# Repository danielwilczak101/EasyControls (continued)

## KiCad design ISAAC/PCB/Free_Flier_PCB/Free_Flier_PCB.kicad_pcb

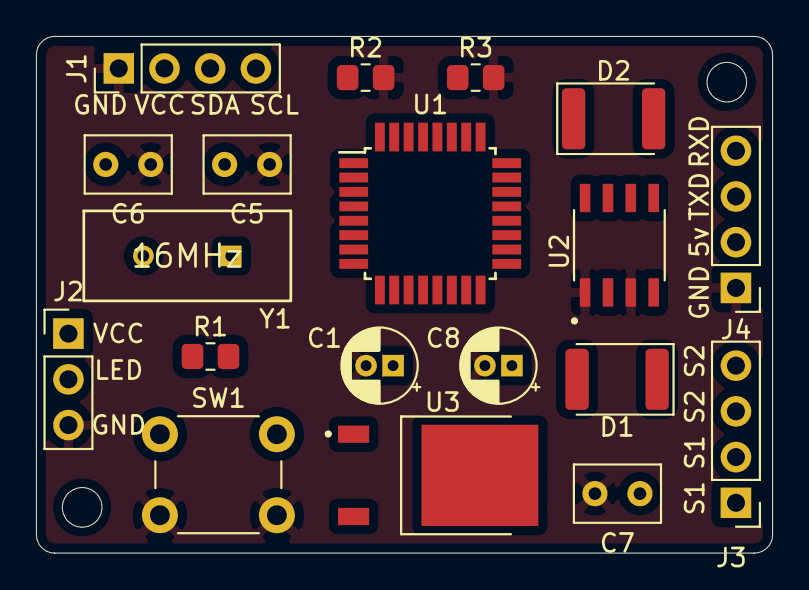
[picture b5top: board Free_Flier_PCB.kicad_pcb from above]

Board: 2 copper layers, 40.9 x 28.7 mm, 21 parts (0 on the bottom side), 12 nets, no tracks yet.

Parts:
C1: 10uF; CP_Radial_D4.0mm_P1.50mm
C5, C6: 22pF; C_Rect_L4.6mm_W3.0mm_P2.50mm_MKS02_FKP02
C7: 0.33uF; C_Rect_L4.6mm_W3.0mm_P2.50mm_MKS02_FKP02
C8: 0.1uF; CP_Radial_D4.0mm_P1.50mm
D1, D2: DIODE; D_1812_4532Metric_Pad1.30x3.40mm_HandSolder
H1, H2: MountingHole; MountingHole_2.2mm_M2
J1: Power and Data Female; PinHeader_1x04_P2.54mm_Vertical
J2: LED Female; PinHeader_1x03_P2.54mm_Vertical
J3: Solenoid Conn; PinHeader_1x04_P2.54mm_Vertical
J4: Programming Pins Female; PinHeader_1x04_P2.54mm_Vertical
R1, R2, R3: 10K; R_0805_2012Metric_Pad1.20x1.40mm_HandSolder
SW1: SW_Push_Dual; SW_PUSH_6mm
U1: ATmega328P-AU; TQFP-32_7x7mm_P0.8mm
U2: DMN4026SSD; SOIC127P600X150-8N
U3: LM78M05CDTX/NOPB; TO228P991X255-3N
Y1: 16MHz; Abracon-ABL-16.000MHZ-B2-0

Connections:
+5V: C1.1, C8.1, J4.2, R1.1, SW1.1, U1.4 (VCC), U1.6 (VCC), U1.18 (AVCC), U1.20 (AREF), U3.1 (OUT)
/Gate1: R2.1, U1.10 (PD6), U2.2 (G1)
/Gate2: R3.1, U1.11 (PD7), U2.4 (G2)
/LED: J2.2, U1.9 (PD5)
/RXD: J4.4, U1.30 (PD0)
/SCL: J1.4, U1.28 (PC5)
/SDA: J1.3, U1.27 (PC4)
/SOL1: D1.1 (K), J3.1, U2.5 (D1), U2.6 (D1)
/SOL2: D2.1 (K), J3.3, U2.7 (D2), U2.8 (D2)
/TXD: J4.3, U1.31 (PD1)
GND: C1.2, C5.1, C6.1, C7.2, C8.2, J1.1, J2.3, J4.1, R2.2, R3.2, SW1.2, U1.3 (GND), U1.5 (GND), U1.21 (GND), U2.1 (S1), U2.3 (S2)
VCC: C7.1, D1.2 (A), D2.2 (A), J1.2, J2.1, J3.2, J3.4, U3.3 (IN)

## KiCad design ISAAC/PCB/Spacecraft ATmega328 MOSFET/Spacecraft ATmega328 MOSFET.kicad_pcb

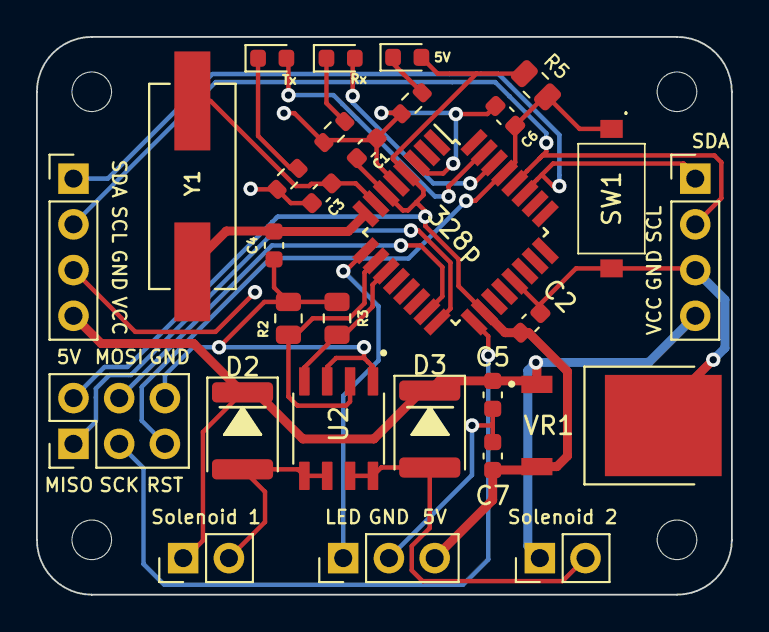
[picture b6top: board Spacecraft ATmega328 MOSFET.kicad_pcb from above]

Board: 2 copper layers, 38.6 x 31.0 mm, 33 parts (0 on the bottom side), 21 nets.

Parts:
5V: LED; LED_0603_1608Metric
328p: ATmega328P-AU; TQFP-32_7x7mm_P0.8mm
C1, C2, C6: 100nF; C_0603_1608Metric
C3, C4: 22pf; C_0603_1608Metric
C5: 0.33 uF; C_0603_1608Metric
C7: 0.1uF; C_0603_1608Metric
D2, D3: D; D_1812_4532Metric
H1, H2, H3, H4: MountingHole; MountingHole_2.2mm_M2
J1, J2: I2C/Power_IN; PinHeader_1x04_P2.54mm_Vertical
J3: Bootloader Pins; PinHeader_2x03_P2.54mm_Vertical
J4: LED; PinHeader_1x03_P2.54mm_Vertical
J5: SOL_1; PinHeader_1x02_P2.54mm_Vertical
Jv: SOL_2; PinHeader_1x02_P2.54mm_Vertical
R2, R3, R5: 10k; R_0805_2012Metric
R6, R7, R8: 300; R_0603_1608Metric
Rx: LED; LED_0603_1608Metric
SW1: SW_Push; PTS636SK25SMTRLFS
Tx: LED; LED_0603_1608Metric
U2: DMN4026SSD; SOIC127P600X150-8N
VR1: LM78M05CDTX_NOPB; TO228P991X255-3N
Y1: Crystal; XTAL_ECS-160-20-5PXDN-TR

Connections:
+5V: 5V.2, 328p.4, 328p.6, 328p.18, C1.1, C2.1, C7.1, J3.2, J4.3, R5.1, VR1.3
/Gate1: 328p.10, R2.1, U2.2
/Gate2: 328p.11, R3.1, U2.4
/LED: 328p.9, J4.1
/MISO: 328p.16, J3.1
/MOSI: 328p.15, J3.4
/RXD: 328p.30, Rx.2
/Reset: 328p.29, C6.2, J3.5, R5.2, SW1.1
/SCK: 328p.17, J3.3
/SCL: 328p.28, J1.2, J2.2
/SDA: 328p.27, J1.1, J2.1
/SOL1: D2.2, J5.2, U2.5, U2.6
/SOL2: D3.2, Jv.2, U2.7, U2.8
/TXD: 328p.31, Tx.2
GND: 328p.3, 328p.5, 328p.21, C1.2, C2.2, C3.1, C4.1, C5.2, C6.1, C7.2, J1.3, J2.3, J3.6, J4.2, R2.2, R3.2, R6.1, R7.1, R8.1, SW1.2, U2.1, U2.3, VR1.4
unnamed: 328p.7, C3.2, Y1.1
unnamed: 328p.8, C4.2, Y1.2
unnamed: 5V.1, R6.2
unnamed: R7.2, Tx.1
unnamed: R8.2, Rx.1
VCC: C5.1, D2.1, D3.1, J1.4, J2.4, J5.1, Jv.1, VR1.1

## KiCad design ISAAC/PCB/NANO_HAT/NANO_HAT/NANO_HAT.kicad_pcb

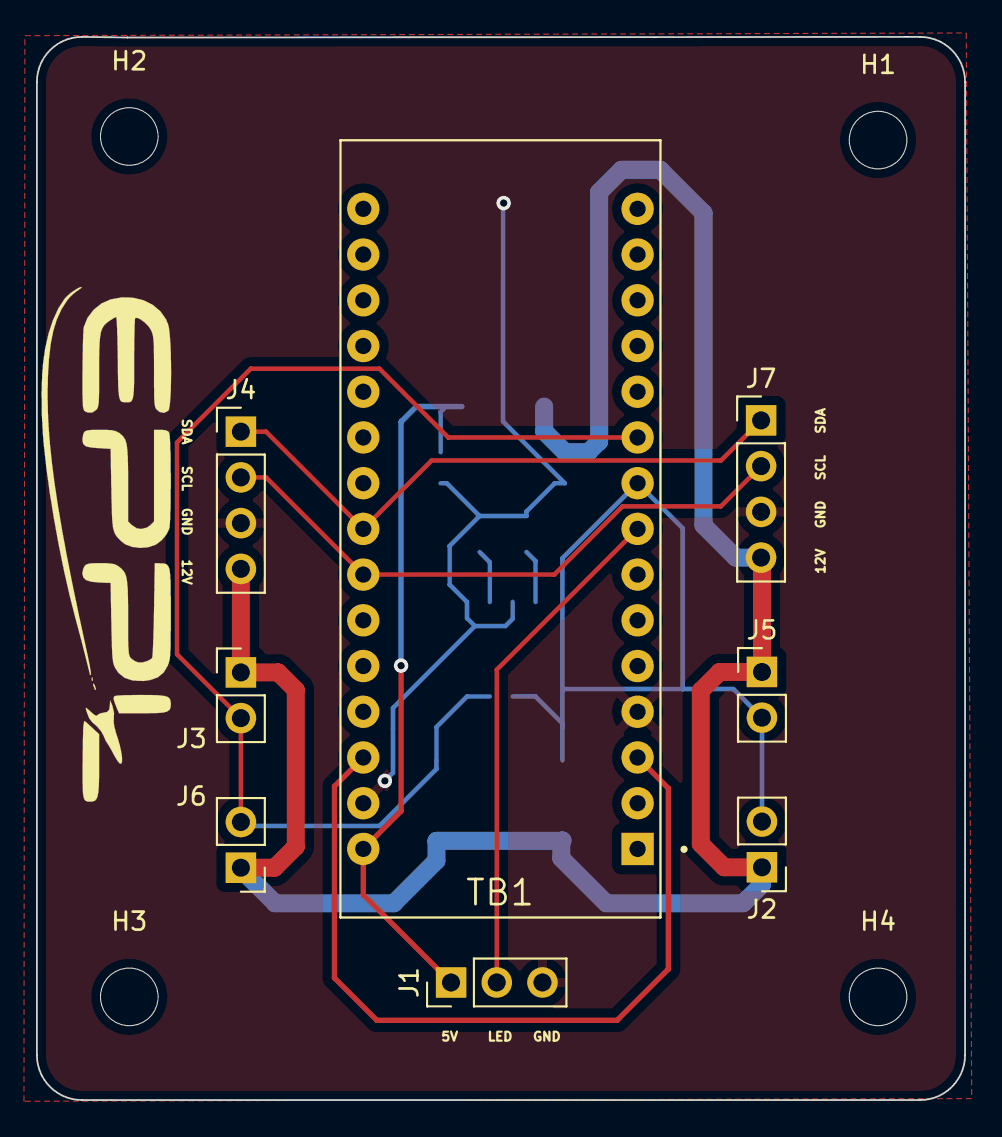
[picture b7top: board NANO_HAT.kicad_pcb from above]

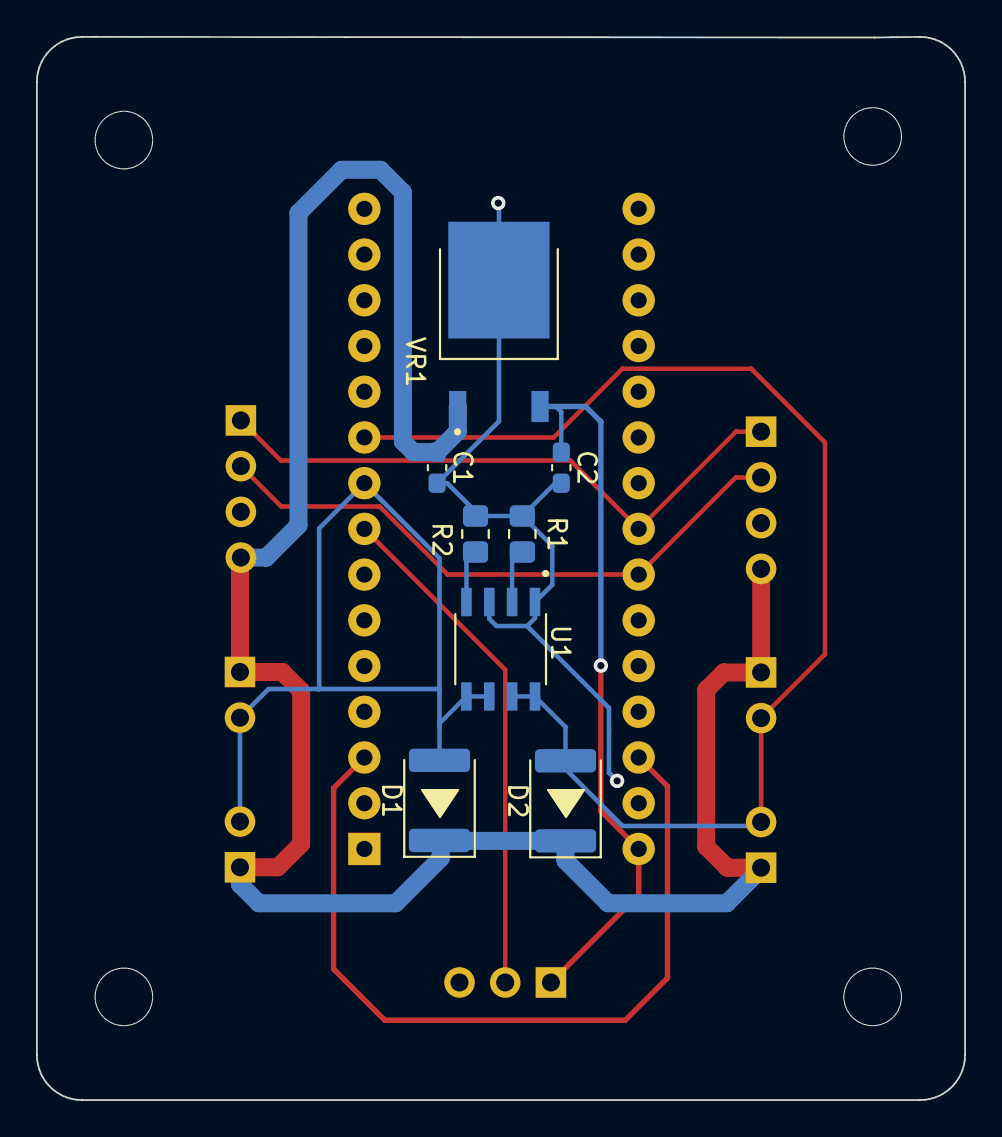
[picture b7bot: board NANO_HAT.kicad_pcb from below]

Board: 2 copper layers, 51.6 x 59.1 mm, 20 parts (8 on the bottom side), 10 nets.

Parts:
C1: 0.33 uF; C_0603_1608Metric_Pad1.08x0.95mm_HandSolder
C2: 0.1uF; C_0603_1608Metric_Pad1.08x0.95mm_HandSolder
D1, D2: D; D_1812_4532Metric_Pad1.30x3.40mm_HandSolder
H1, H2, H3, H4: MountingHole; MountingHole_3.2mm_M3
J1: Conn_01x03_Male; PinHeader_1x03_P2.54mm_Vertical
J2, J3, J5, J6: Conn_01x02_Male; PinHeader_1x02_P2.54mm_Vertical
J4, J7: Conn_01x04_Male; PinHeader_1x04_P2.54mm_Vertical
R1, R2: 10k; R_0805_2012Metric_Pad1.20x1.40mm_HandSolder
TB1: ARDUINO_NANO; SHIELD_ARDUINO_NANO
U1: DMN4026SSD; SOIC127P600X150-8N
VR1: LM78M05CDTX/NOPB; TO228P991X255-3N

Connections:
/5V: C2.1, J1.1, TB1.30 (VIN), VR1.3 (OUTPUT)
/Gate 1: R1.2, U1.2 (G1)
/Gate 2: R2.2, U1.4 (G2)
/LED: J1.2, TB1.8 (D5)
/SCL: J4.2, J7.2, TB1.24 (A5)
/SDA: J4.1, J7.1, TB1.23 (A4)
/SOL1: D1.2 (A), J2.2, J5.2, TB1.9 (D6), U1.5 (D1), U1.6 (D1)
/SOL2: D2.2 (A), J3.2, J6.2, TB1.10 (D7), U1.7 (D2), U1.8 (D2)
GND: C1.2, C2.2, J1.3, J4.3, J7.3, R1.1, R2.1, TB1.4 (COM/GND), TB1.29 (COM/GND), U1.1 (S1), U1.3 (S2), VR1.4 (GND)
VCC: C1.1, D1.1 (K), D2.1 (K), J2.1, J3.1, J4.4, J5.1, J6.1, J7.4, VR1.1 (INPUT)

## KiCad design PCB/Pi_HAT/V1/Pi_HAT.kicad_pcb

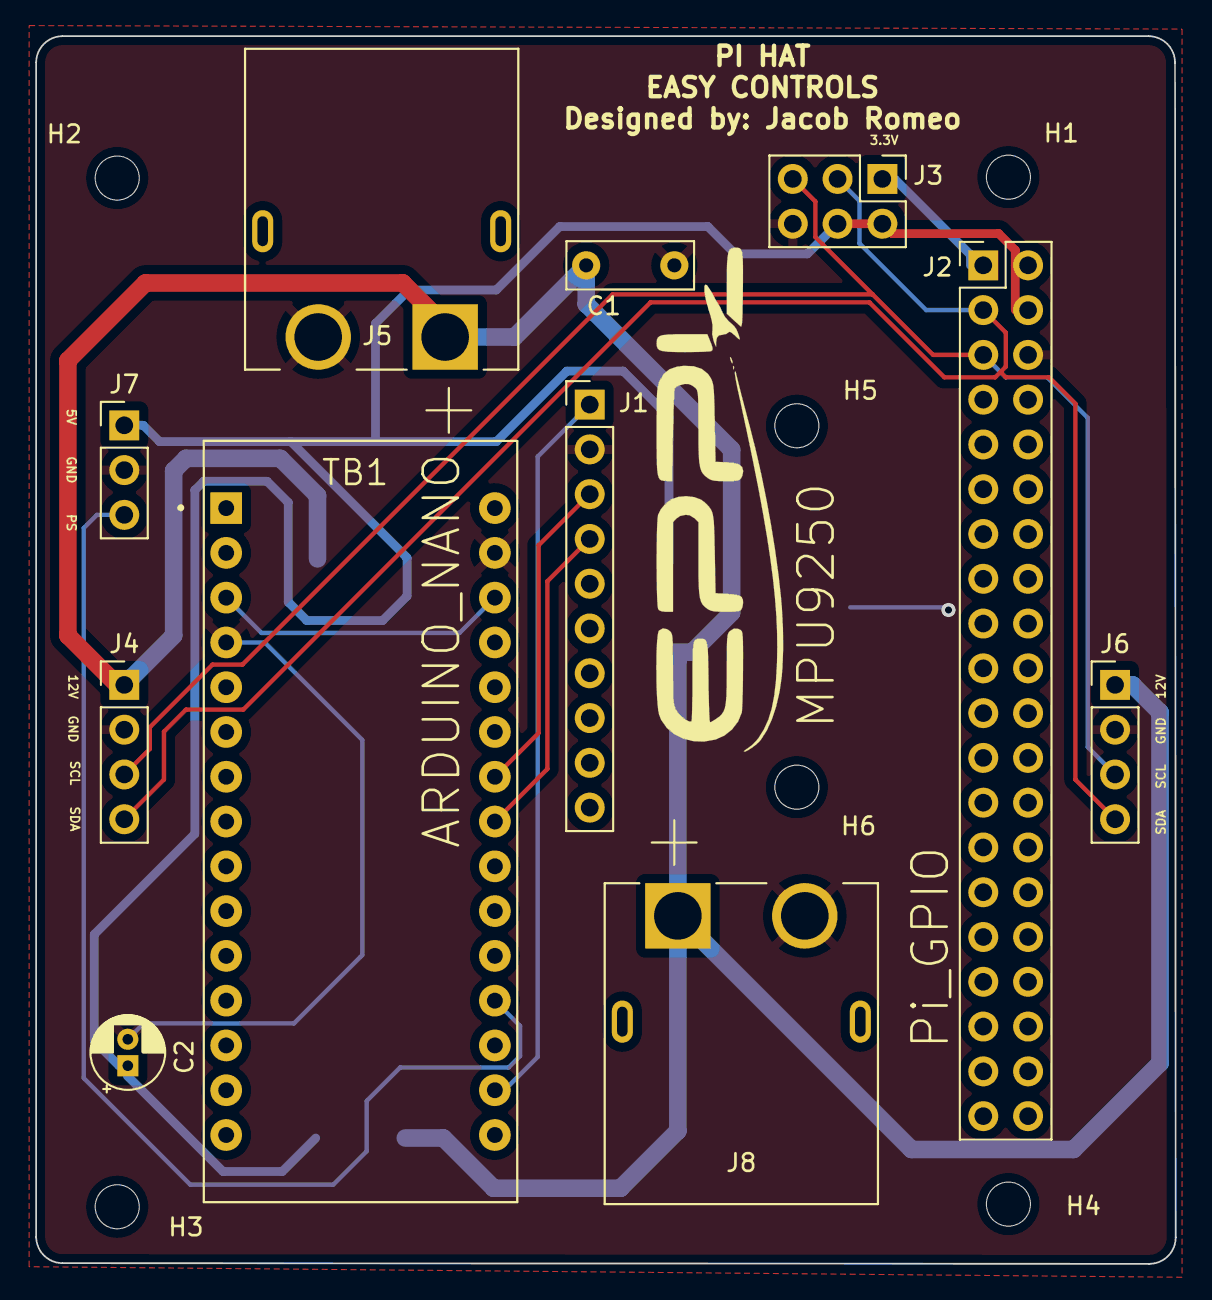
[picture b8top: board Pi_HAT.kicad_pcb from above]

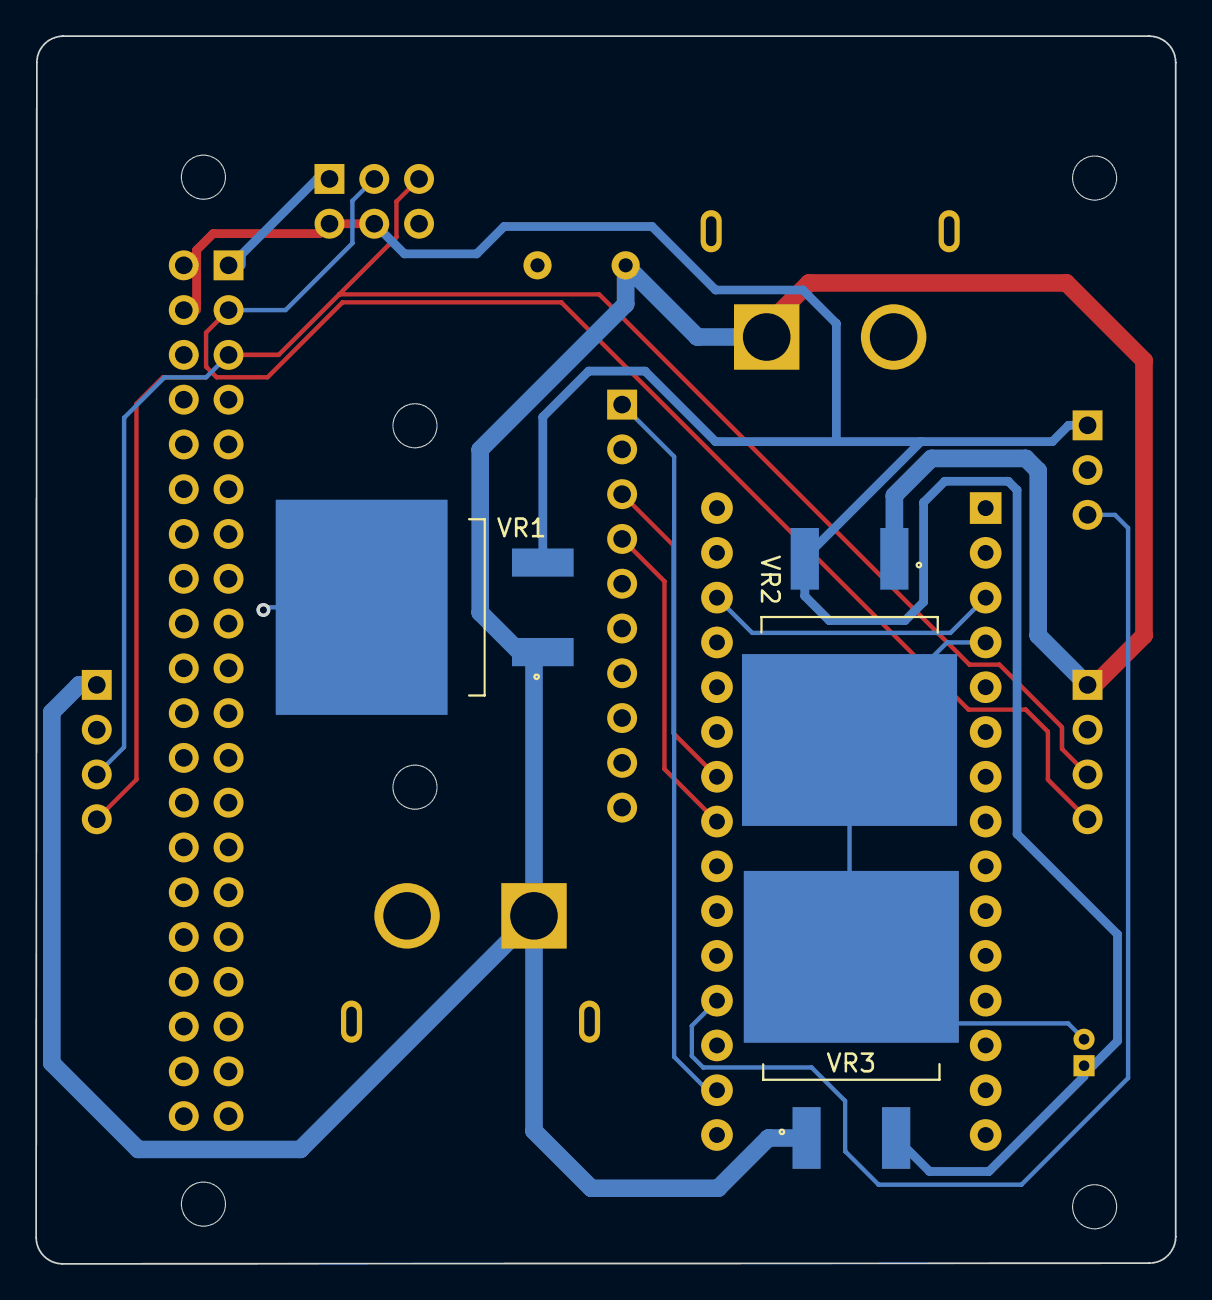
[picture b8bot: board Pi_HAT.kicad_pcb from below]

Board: 2 copper layers, 64.6 x 69.6 mm, 20 parts (3 on the bottom side), 10 nets.

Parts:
C1: C; C_Rect_L7.0mm_W2.5mm_P5.00mm
C2: C_Polarized; CP_Radial_D4.0mm_P1.50mm
H1, H2, H3, H4, H5, H6: MountingHole; MountingHole_2.5mm
J1: MPU9250; PinHeader_1x10_P2.54mm_Vertical
J2: Pi_GPIO; PinHeader_2x20_P2.54mm_Vertical
J3: Display; PinHeader_2x03_P2.54mm_Vertical
J4, J6: Solenoid I2C; PinHeader_1x04_P2.54mm_Vertical
J5, J8: XT60PW-M; AMASS_XT60PW-M
J7: Pressure; PinHeader_1x03_P2.54mm_Vertical
TB1: ARDUINO_NANO; SHIELD_ARDUINO_NANO
VR1, VR2, VR3: LM78M05CDTX/NOPB; VREG_L7805ACD2T

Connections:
3.3VN: J1.1, TB1.17 (3V3)
3.3VP: J2.1, J3.1
12V: C1.1, J4.1, J5.1 (+), J6.1, J8.1 (+), VR1.1 (INPUT), VR2.1 (INPUT), VR3.1 (INPUT)
/5V: C2.1, J2.2, J2.4, J3.2, J3.4, J7.1, VR1.3 (OUTPUT), VR2.3 (OUTPUT), VR3.3 (OUTPUT)
/PS: J7.3, TB1.19 (A0)
/SCL: J2.5, J3.5, J4.3, J6.3
/SDA: J2.3, J3.3, J4.4, J6.4
GND: C1.2, C2.2, J1.2, J2.6, J3.6, J4.2, J5.2 (-), J6.2, J7.2, J8.2 (-), TB1.4 (COM/GND), TB1.29 (COM/GND), VR1.4 (GND), VR2.4 (GND), VR3.4 (GND)
SCLN: J1.3, TB1.24 (A5)
SDAN: J1.4, TB1.23 (A4)

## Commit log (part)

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2022-08-22 Pi_HAT V2
2022-08-22 Still more to do
2022-09-02 Updated code
2022-09-02 Updated thruster numbers
2022-09-02 Thruster number test
2022-09-02 updated error
2022-09-02 Added close feature
2022-09-02 Gave time to close at end of test.
2022-09-02 testing bottom
2022-09-02 Testing spin.
2022-09-02 Updated website code to add thrusters.
2022-09-02 chnaging again.
2022-09-02 revert back
2022-09-02 updated to make it async
2022-09-02 Updated website
2022-09-02 fixed
2022-09-03 Updated async version
2022-09-03 Update to find str
2022-09-03 Added exception.
2022-09-03 Checking axis
2022-09-03 Removed sleep
2022-09-03 updated print
2022-09-03 Added gyro scope
2022-09-03 Fixed sleep
2022-09-03 Updated with gyro balance
2022-09-03 Added to threshold
2022-09-03 Added
2022-09-03 Updated threshold
2022-09-03 updatwd
2022-09-03 Removed bus
2022-09-03 Changed angle
2022-09-07 Trying
2022-09-07 We'll see what happens
2022-09-07 Nothing is happening
2022-09-08 Finished Buch .sch
    Next need to start/finish the PCB traces
2022-09-08 Added Extra I2C Header
2022-09-08 Gerber for V1 Pi_HAT
    Order this one along with the Buck Converter PCB
2022-09-10 Updated
    Added NANO_HAT and finished the PI_HAT V2 .sch, need to start/finish traces
2022-09-12 Updated V1 Pi Hat
2022-09-13 Fixed csv and added "go crazy"
2022-09-13 Fixed typos and changed "go crazy"
2022-09-13 Added velocity to the gyro data
2022-09-13 Print velocity
2022-09-14 Created NANO_HAT
2022-09-14 updated NANO_HAT
2022-09-15 Finished V1
2022-09-15 Updated (Gerber)
2022-09-16 NANO_HAT Update 2
2022-09-19 Finished Pi HAT V2
    Double checked all 'new' PCB's and made gerbers for all along with a BOM.
2022-09-23 Added CubeSat PCB
    Still needs to be finished
2022-09-23 Finished/Uploaded Gerber
2022-09-23 .step
2022-09-25 Updated examples
2022-09-25 Moved
2022-09-25 Updated with move
2022-09-25 Folder cleanup
2022-10-02 Made BOM file // READY to order
2022-10-03 Fixed NANO_HAT
2022-10-03 Uploaded Gerber
2022-10-03 Updated V2 Pi HAT CSV
2022-10-04 Add README
2022-10-04 Added angle code
2022-10-04 Added images
2022-10-04 Added image
2022-10-05 Deleted unnecessary files
2022-10-05 Deleted MPU6050 file
2022-10-05 Delete IMG_2099.jpg
    Not in correct folder
2022-10-05 Delete IMG_2100.jpg
    Not in correct folder
2022-10-05 Added Header
2022-10-06 Coded motor test
2022-10-06 Fixed eror
2022-10-06 Fixed error
2022-10-06 Moved some files around for CubeSat
2022-10-06 Nothing
2022-10-06 changed freq
2022-10-06 Upped duty cycle
2022-10-06 Changed direction and brake
2022-10-06 Changed brake
2022-10-06 While loop for PWM
2022-10-06 Commented out while
2022-10-06 Uncommented while loop
2022-10-06 Upped delay
2022-10-06 Changed while loop
2022-10-06 Changed while
2022-10-06 Added max speed
2022-10-06 Coded mpu_motor
2022-10-06 Error check
2022-10-06 Changed pins
2022-10-06 No zen
2022-10-06 Made target angle a range
2022-10-06 Changed axis
2022-10-07 changed lots
2022-10-07 added error for target
2022-10-07 Error checkk
2022-10-07 added print statements
2022-10-07 added range
2022-10-07 added thing
2022-10-07 changed max speed
2022-10-08 Updated code to handle warning
2022-10-08 Moved warning removal
2022-10-08 Udated loop
2022-10-08 UOpdated
2022-10-08 Added gpio change code.
2022-10-08 Updated pin direction
2022-10-08 Updated freq
2022-10-08 test
2022-10-08 Fixed PCB
2022-10-13 Wrote code
2022-10-13 made it python
2022-10-13 Added infinity
2022-10-14 adsfja
2022-10-14 Things
2022-10-14 lost the async
2022-10-14 added for loop
2022-10-14 udpate
2022-10-14 updated parameters
2022-10-14 udpaed
2022-10-14 chagned angle
2022-10-14 cleared faults
2022-10-14 changed things
2022-10-14 added parameters
2022-10-14 chagned
2022-10-14 lodt for loop
2022-10-14 changed position
2022-10-14 cdsv
2022-10-14 fdsf
2022-10-14 added while loop
2022-10-14 miracles
2022-10-14 udated
2022-10-14 acadc
2022-10-14 dsad
2022-10-14 fast
2022-10-16 for loop
2022-10-16 sdfsd
2022-10-16 sasa
2022-10-16 dsds
2022-10-16 udpated
2022-10-16 printing things
2022-10-16 dsdsd
2022-10-16 xzxz
2022-10-16 reverse
2022-10-16 dwdw
2022-10-16 whiled
2022-10-16 dsdssd
2022-10-17 Lost max velocity
2022-10-17 max vel
2022-10-17 syntax error
2022-10-17 changed
2022-10-17 v cap
2022-10-17 added folder
2022-10-17 position
2022-10-17 fdfd
2022-10-22 Updated ISAAC & CubeSat
    Created Pi HAT V3 PCB and new CubeSat PCB
2022-10-24 Updated Moteus PCB
2022-10-28 Update solenoid.ino
    Updated neo pin name.
2022-10-29 Updated CubeSat PCB
    Still need the dimensions for the CAN bus converter
2022-10-31 Updated CubeSat PCB
2022-11-02 Traced V3
2022-11-03 Finished CubeSat PCB
    Uploaded gerber.zip
2022-11-04 Added .step file
2022-11-11 Changed max velocity
2022-11-11 added simple.py file
2022-11-13 Made position control sinisoidal
2022-11-13 Made position control sin wave
2022-11-13 Confirmed position_control worked
2022-11-13 Added start/stop code
2022-11-13 editted start/stop code
2022-11-13 added print statement
2022-11-13 fixed for loop
2022-11-13 increased max torquw
2022-11-13 added target position
2022-11-13 increased delay
2022-11-13 added max slip
2022-11-13 added goal velocity
2022-11-13 edit
2022-11-13 lowered vel
2022-11-14 Changed velocity
2022-11-14 Changed velo
2022-11-14 max torquee
2022-11-14 added brake
2022-11-14 added delay
2022-11-14 lowered delay
2022-11-14 Editted it
2022-11-21 Shit ton of stuf
2022-11-23 Final Updates "HOPEFULLY"
2022-11-24 modified: Start_Stop.py motor_control.py mpu_degrees.py
2022-11-26 Cleaned up moteus folder; added motor/mpu script
2022-11-28 Added new file: PID control
2022-11-29 Editted
2022-11-29 Added PID!
2022-11-29 Updated final
2022-12-02 added stop motor file
2023-02-06 Created multiple_motor test
2023-02-20 Added 1DoF Pid
2023-02-21 Added basic if else control loop
2023-02-21 Changed Angle Acquisition Process
2023-02-22 Solved Angle Problem. Range from 0 to 360
2023-02-22 Housekeeping in Moteus Folder
2023-02-24 Added Moteus documentation
2023-02-24 Fixed minor errors in Moteus documentation
2023-02-24 Create hardwaresetup reference page
2023-02-25 Fixed minor mistake
2023-02-26 new file: Variations Curve.png
2023-02-26 new file: Variations Curve2.png
2023-02-26 new file: Variations Curve.png fileClean.py
2023-02-27 Updated hardwaresetup readme
2023-02-27 modified: Variations Curve.png
2023-02-28 Auto stash before merge of "main" and "origin/main"
2023-03-08 Added multimotorcontrol file
2023-03-09 Added IMU File
2023-03-22 modified: website.py
2023-03-24 Updated PID code
2023-04-03 Added code for 9DOF Board
2023-05-04 Sliding mode update
2023-09-06 Updated code: Sorta works
2023-09-18 Updated
    Started SPARK grant and updated controller and PCB
2023-11-01 Docs
2024-01-24 Updated ISAAC PCB
2024-01-24 Updated lmao
2024-02-05 Updated pcb
2024-03-04 made new V5 PCB
2024-04-03 add sliding mode controller with database loging
2024-04-03 set s float and u int for database
2024-04-03 update database to log kd and target
2024-04-08 added pressure stuff
2024-04-19 updated spie
2024-04-27 add code to stream imu data to unity
2024-04-27 update unity to have prints and run until program killed
2024-04-27 update how data is sent to unity, new line at end of msg
2024-04-27 get rid of new line send
2024-04-27 updaet
2024-05-02 update port
2024-09-28 Creating DOC! Finally! Pls Don't forget about me!
2024-09-28 lets see if this makes the docs work
2024-09-28 update docs.... maybe it will work this time
2024-09-28 dan says this will work
2024-09-28 maybe this will work
2024-09-28 now third time is the charm
2024-09-28 now this should really work I promise
2024-09-28 Updated using linux and not trash windows \
2024-09-28 Deployed 97485c2 with MkDocs version: 1.6.1
